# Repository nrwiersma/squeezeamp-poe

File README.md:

# SqueezeAMP PoE

`SqueezeAMP PoE` is an amplifier driven by an ESP32 designed to run [squeezelite-esp32](https://github.com/sle118/squeezelite-esp32), powered by PoE++.

Features:

* Power over Ethernet 802.3bt 60W (PoE++)
* ESP32 WROOM 4MB Flash 8MB PSRAM
* TAS5756 Amplifier capable of driving stereo 30W 8Ohm speakers

## Why

The position of speakers is often not optimal for WiFi, leading to unreliable music streaming. Adding 100Mb ethernet allows
more reliable connections with ample bandwidth. Given an ethernet connection, PoE is able to provide power for the device.

The schematic is inspired by the [SqueezeAMPagain](https://github.com/hallo-alex/SqueezeAMPagain).

## Configuration

Install [squeezelite-esp32](https://github.com/sle118/squeezelite-esp32). The simplest method is to use the [installer](https://sle118.github.io/squeezelite-esp32-installer/).

Set the following configuration via the NVS Editor to configure:

dac_config: `model=TAS57xx,bck=33,ws=25,do=32,sda=27,scl=26,mute=4:0`
eth_config: `model=w5500,cs=15,speed=20000000,intr=18,rst=19`
spi_config: `mosi=13,clk=14,host=1,miso=12,dc=-1`
set_GPIO:   `2=spkfault`

## PCB Fabrication and Assembly by PCBWay

I am proudly sponsored by [PCBWay](https://www.pcbway.com/), a leading manufacturer specializing in PCB prototyping, 
low-volume production, and PCB Assembly services. Thanks to PCBWay’s sponsorship, I was able to fabricate and assemble 
my PCBs with high precision and quality. Their advanced manufacturing capabilities ensured that our design was 
translated into a robust and functional product.

[//]: # (![board image]&#40;assets/pcb.png&#41;)

### Why PCBWay?

PCBWay offers:

* **High-quality PCB fabrication** with multiple layer options, surface finishes, and material choices.
* **Fast turnaround times** to meet project deadlines efficiently.
* **Affordable pricing** for both prototyping and mass production.
* **Reliable PCB assembly services**, including SMT, through-hole, and mixed assembly.
* **Exceptional customer support** and a user-friendly ordering platform.

### Get Your Own PCBs from PCBWay

I highly recommend PCBWay for all your PCB fabrication and assembly needs. Their dedication to quality and customer 
satisfaction makes them an ideal partner for your projects. If you're looking for a trusted partner for PCB fabrication 
and assembly, check out PCBWay for your next project.

Special thanks to PCBWay for their generous support!

## Changelog

#### v0.1.0

* Initial schematic and board

#### v0.1.1

* Fixed W5500 crystal clock not being enabled

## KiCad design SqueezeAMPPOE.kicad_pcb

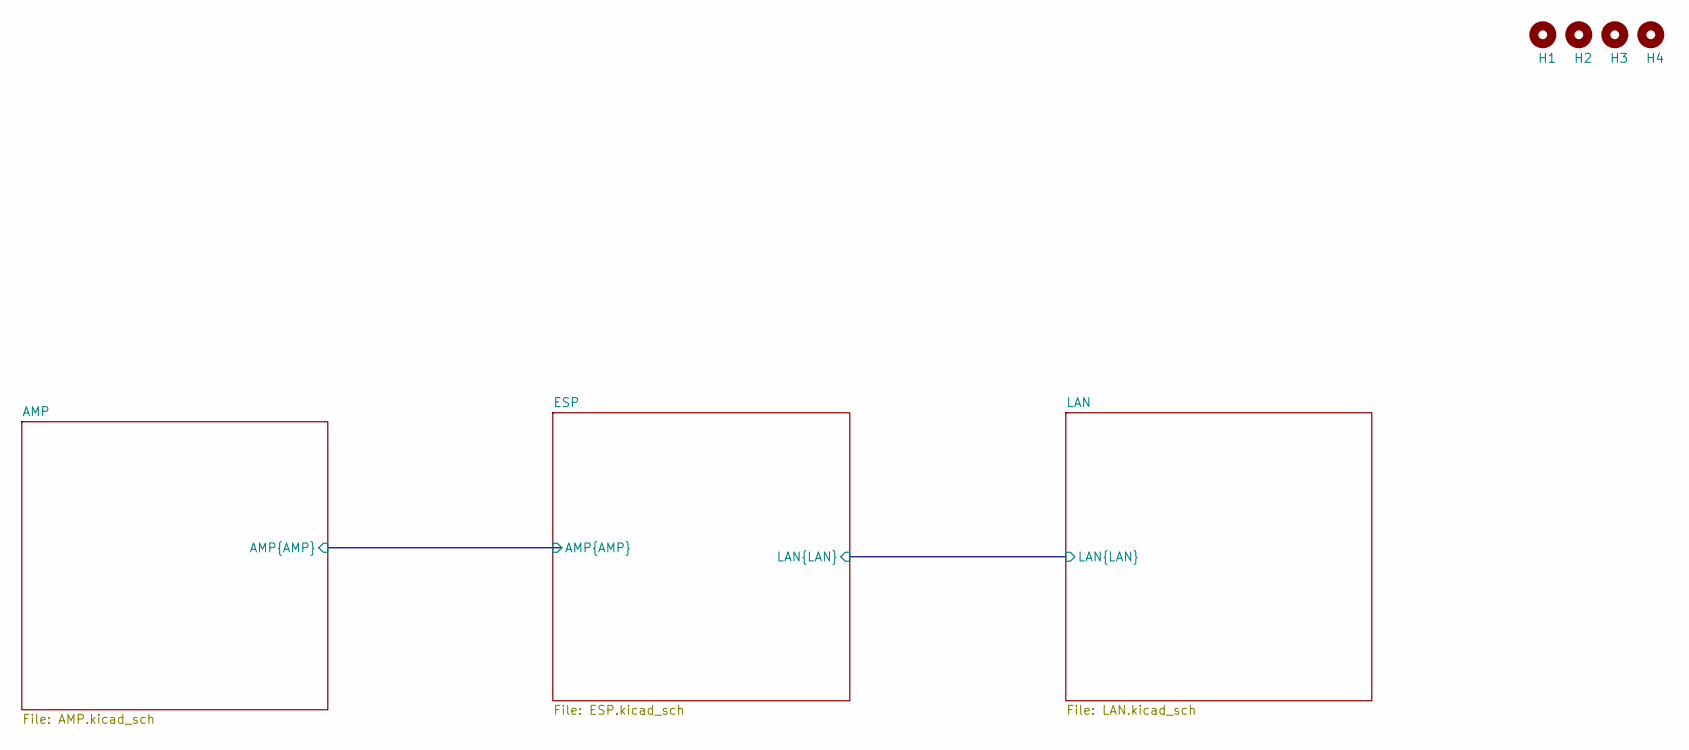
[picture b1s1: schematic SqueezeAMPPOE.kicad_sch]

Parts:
H1, H2, H3, H4: MountingHole; MountingHole_3.2mm_M3

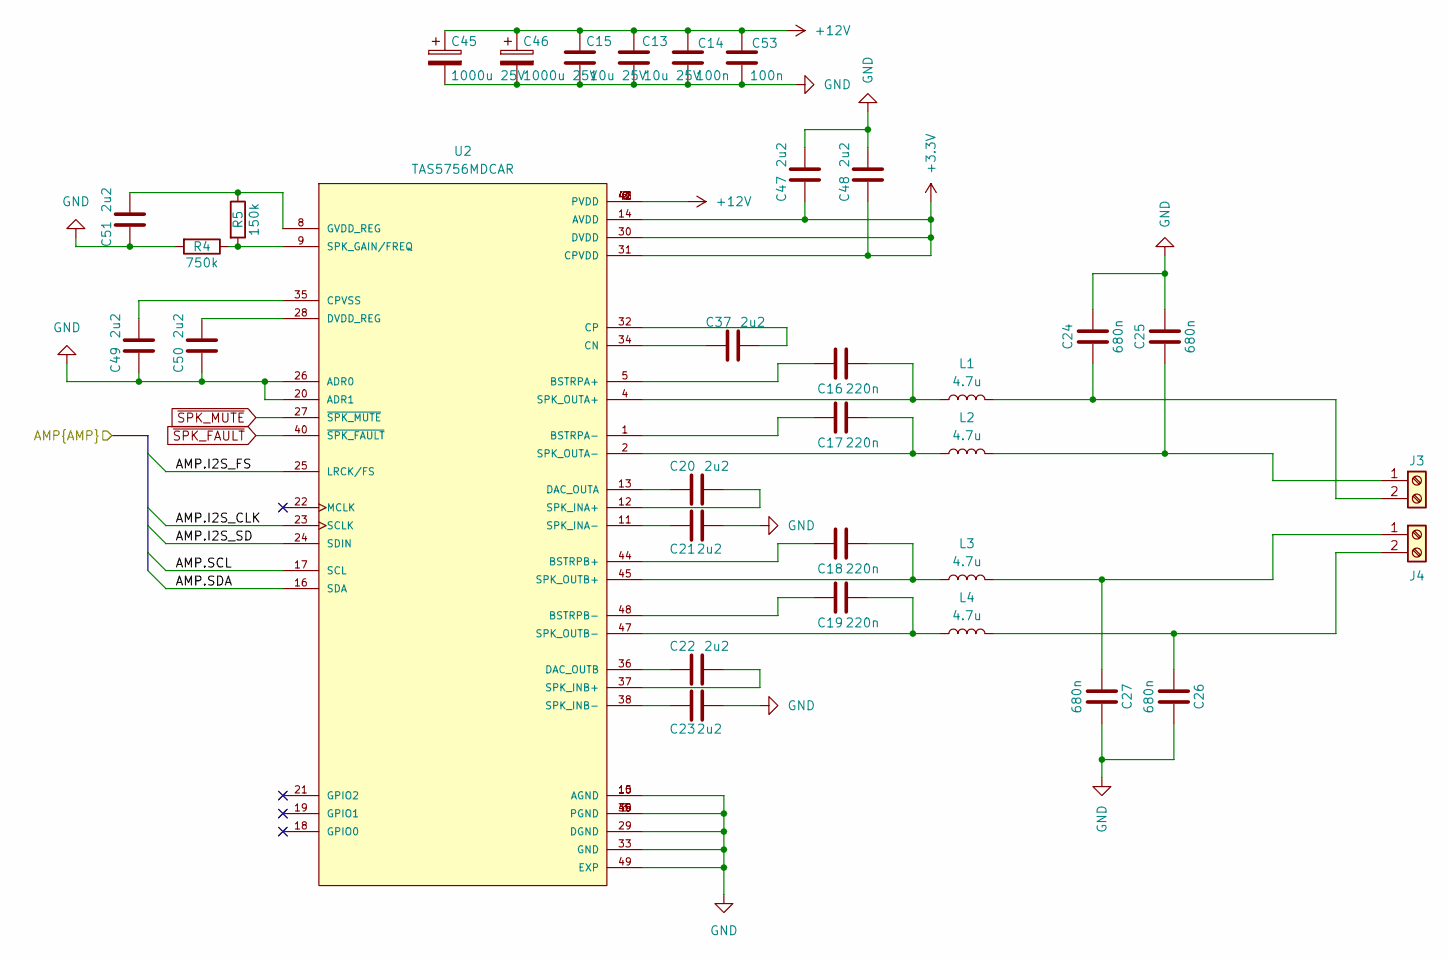
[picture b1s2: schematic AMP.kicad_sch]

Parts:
C13, C15: 10u 25V; C_0603_1608Metric; MPN CL10A106MA8NRNC; JLCPCB Part # C96446
C14, C53: 100n; C_0603_1608Metric; MPN CL10B104KB8NNNC; JLCPCB Part # C1591
C16, C17, C18, C19: 220n; C_0805_2012Metric; MPN CL21B224KBFNNNE; JLCPCB Part # C5378
C20, C21, C22, C23, C37, C47, C48, C49, C50, C51: 2u2; C_0603_1608Metric; MPN CL10A225KA8NNNC; JLCPCB Part # C57895
C24, C25, C26, C27: 680n; C_0805_2012Metric; MPN CC0805KKX7R9BB684; JLCPCB Part # C107133
C45, C46: 1000u 25V; CP_Elec_10x12.5; MPN EFVM025ADA102M10C0; JLCPCB Part # C22387800
J3, J4: Screw_Terminal_01x02; TerminalBlock_Phoenix_MKDS-1,5-2-5.08_1x02_P5.08mm_Horizont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; MPN 1715721; JLCPCB Part # C480516
L1, L2, L3, L4: 4.7u; L_Ferrocore_DLG-0703; MPN SM7850-4R7MT; JLCPCB Part # C52377
R4: 750k; R_0603_1608Metric; MPN RC0603FR-07750KL; JLCPCB Part # C137684
R5: 150k; R_0603_1608Metric; MPN RC0603FR-07150KL; JLCPCB Part # C114660
U2: TAS5756MDCAR; SOP50P810X120-49N; MPN TAS5756MDCAR; JLCPCB Part # C2867541

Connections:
+3.3V: C47.1, C48.1, U2.14 (AVDD), U2.30 (DVDD), U2.31 (CPVDD); also elsewhere on the board
+12V: C13.2, C14.2, C15.2, C45.1, C46.1, C53.2, U2.6 (PVDD), U2.7 (PVDD), U2.41 (PVDD), U2.42 (PVDD), U2.43 (PVDD); also elsewhere on the board
/AMP/AMP.I2S_CLK: U2.23 (SCLK); also elsewhere on the board
/AMP/AMP.I2S_FS: U2.25 (LRCK/FS); also elsewhere on the board
/AMP/AMP.I2S_SD: U2.24 (SDIN); also elsewhere on the board
/AMP/AMP.SCL: U2.17 (SCL); also elsewhere on the board
/AMP/AMP.SDA: U2.16 (SDA); also elsewhere on the board
GND: C13.1, C14.1, C15.1, C21.2, C23.2, C24.2, C25.2, C26.2, C27.2, C45.2, C46.2, C47.2, C48.2, C49.1, C50.1, C51.1, C53.1, R4.2, U2.3 (PGND), U2.10 (AGND), U2.15 (AGND), U2.20 (ADR1), U2.26 (ADR0), U2.29 (DGND), U2.33 (GND), U2.39 (PGND), U2.46 (PGND), U2.49 (EXP); also elsewhere on the board
unnamed: C25.1, J3.1, L2.2
unnamed: C24.1, J3.2, L1.2
unnamed: C27.1, J4.1, L3.2
unnamed: C26.1, J4.2, L4.2
unnamed: C16.1, U2.5 (BSTRPA+)
unnamed: C17.1, U2.1 (BSTRPA-)
unnamed: C18.1, U2.44 (BSTRPB+)
unnamed: C19.1, U2.48 (BSTRPB-)
unnamed: C37.1, U2.34 (CN)
unnamed: C37.2, U2.32 (CP)
unnamed: C49.2, U2.35 (CPVSS)
unnamed: C20.1, U2.13 (DAC_OUTA)
unnamed: C22.1, U2.36 (DAC_OUTB)
unnamed: C50.2, U2.28 (DVDD_REG)
unnamed: C51.2, R5.1, U2.8 (GVDD_REG)
unnamed: R4.1, R5.2, U2.9 (SPK_GAIN/FREQ)
unnamed: C20.2, U2.12 (SPK_INA+)
unnamed: C21.1, U2.11 (SPK_INA-)
unnamed: C22.2, U2.37 (SPK_INB+)
unnamed: C23.1, U2.38 (SPK_INB-)
unnamed: C16.2, L1.1, U2.4 (SPK_OUTA+)
unnamed: C17.2, L2.1, U2.2 (SPK_OUTA-)
unnamed: C18.2, L3.1, U2.45 (SPK_OUTB+)
unnamed: C19.2, L4.1, U2.47 (SPK_OUTB-)
~SPK_FAULT: U2.40 (~SPK_FAULT); also elsewhere on the board
~SPK_MUTE: U2.27 (~SPK_MUTE); also elsewhere on the board

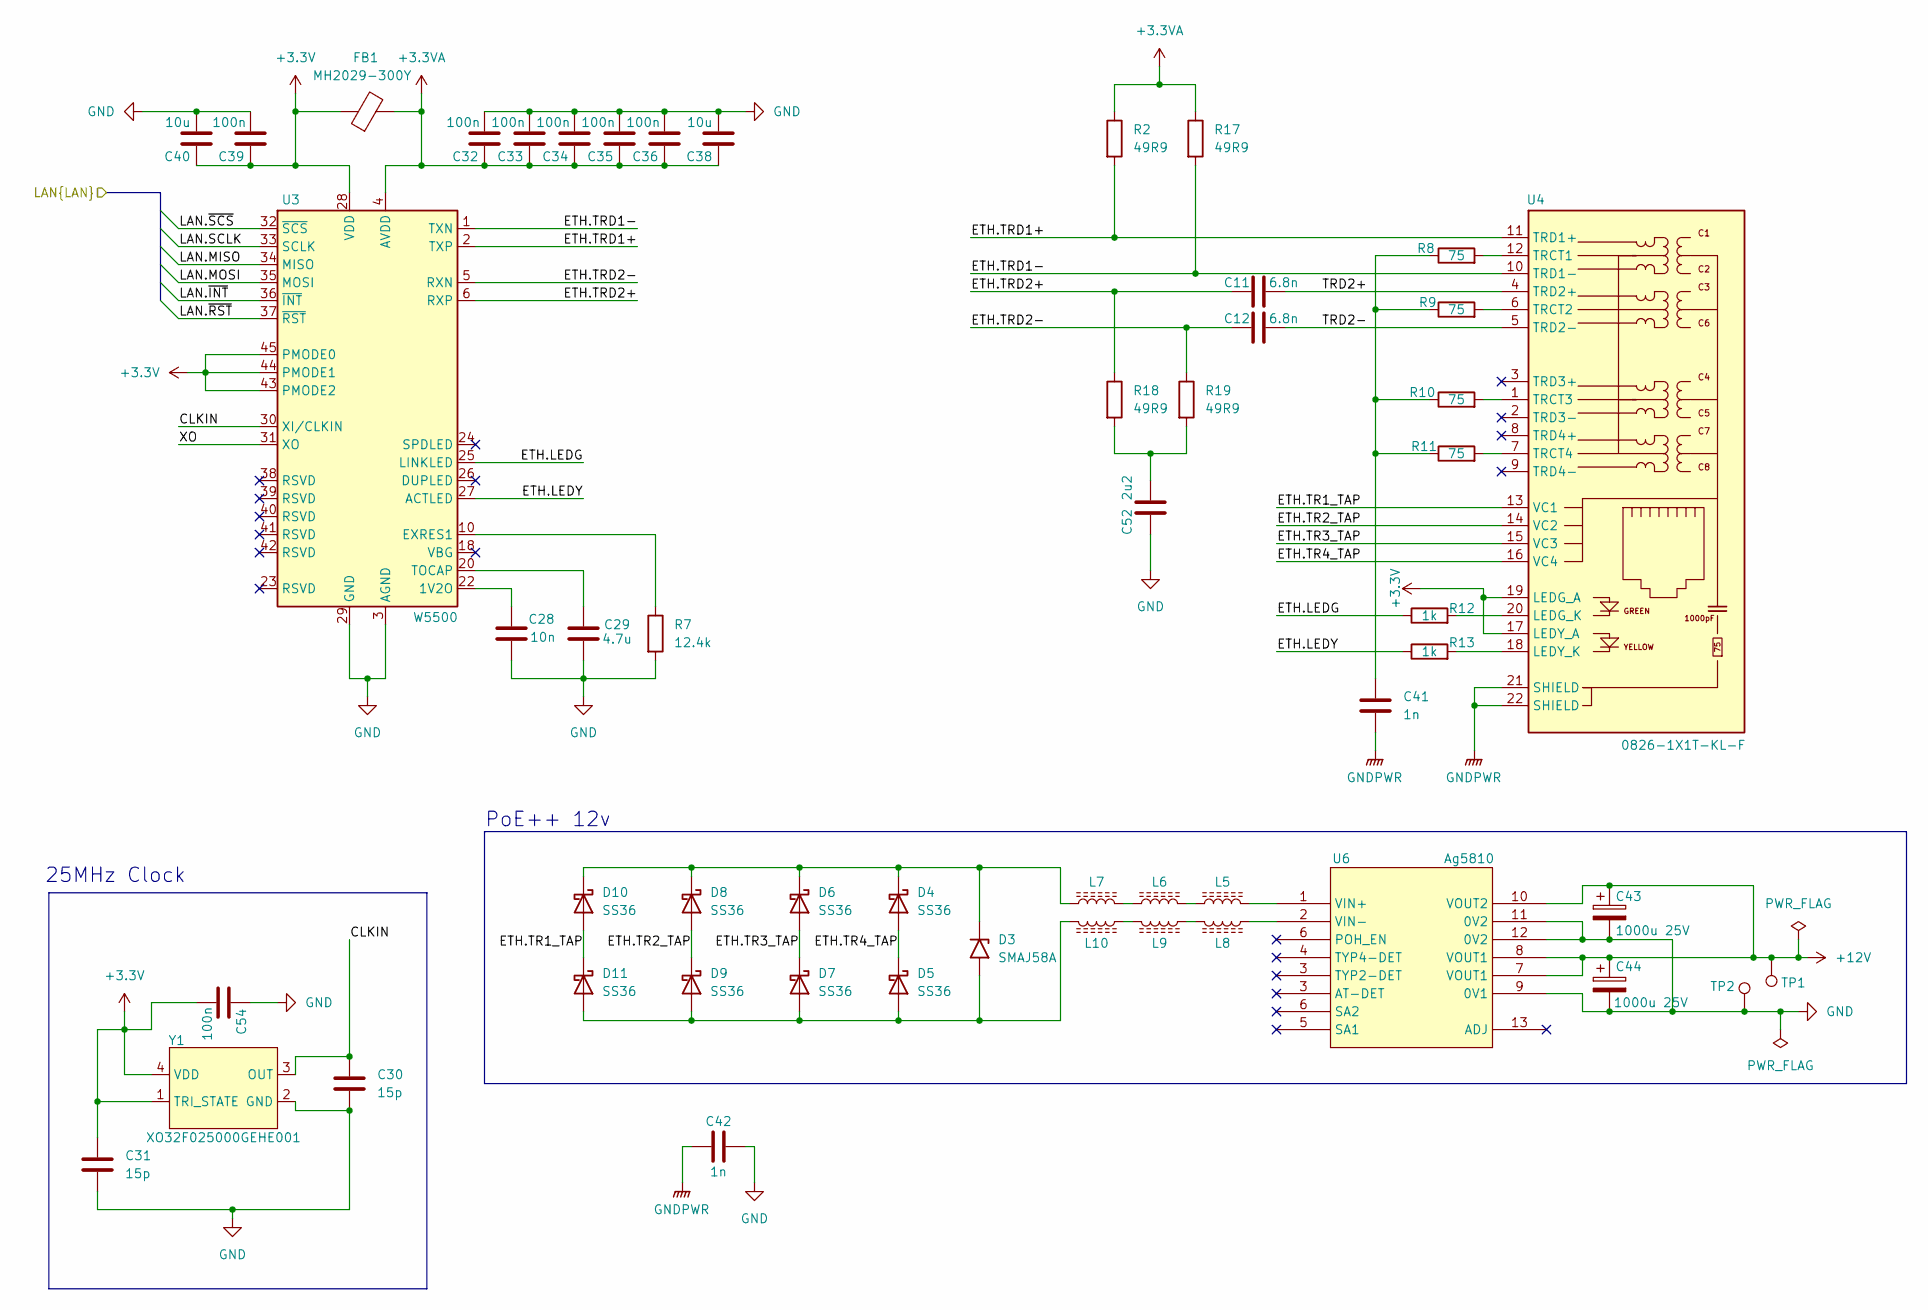
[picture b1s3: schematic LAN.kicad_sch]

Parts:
C11, C12: 6.8n; C_0603_1608Metric; MPN C1608C0G2A682J080AC; JLCPCB Part # C2183110
C28: 10n; C_0603_1608Metric; MPN CL10B103KB8NNNC; JLCPCB Part # C1589
C29: 4.7u; C_0603_1608Metric; MPN CL10A475KP8NNNC; JLCPCB Part # C1705
C30, C31: 15p; C_0603_1608Metric; MPN CL10C150JB8NNNC; JLCPCB Part # C1644
C32, C33, C34, C35, C36, C39, C54: 100n; C_0603_1608Metric; MPN CL10B104KB8NNNC; JLCPCB Part # C1591
C38, C40: 10u; C_0603_1608Metric; MPN CL10A106MA8NRNC; JLCPCB Part # C96446
C41: 1n; C_0603_1608Metric; MPN CL10B102KB8NNNC; JLCPCB Part # C1588
C42: 1n; C_1206_3216Metric; MPN CC1206KKX7RDBB102; JLCPCB Part # C23631
C43, C44: 1000u 25V; CP_Elec_10x12.5; MPN EFVM025ADA102M10C0; JLCPCB Part # C22387800
C52: 2u2; C_0603_1608Metric; MPN CL10A225KA8NNNC; JLCPCB Part # C57895
D3: SMAJ58A; D_SMA; MPN SMAJ58A; JLCPCB Part # C151246
D4, D5, D6, D7, D8, D9, D10, D11: SS36; D_SMA; MPN SS36; JLCPCB Part # C16015
FB1: MH2029-300Y; L0805; MPN MH2029-300Y; JLCPCB Part # C840593
L5, L6, L7, L8, L9, L10: FBMH3225HM102NT; L_1210; MPN FBMH3225HM102NT; JLCPCB Part # C21520
R2, R17, R18, R19: 49R9; R_0603_1608Metric; MPN RC0603FR-0749R9L; JLCPCB Part # C114625
R7: 12.4k; R_0603_1608Metric; MPN RC0603FR-0712K4L; JLCPCB Part # C137798
R8, R9, R10, R11: 75; R_0603_1608Metric; MPN RC0603FR-0775RL; JLCPCB Part # C112309
R12, R13: 1k; R_0603_1608Metric; MPN RC0603JR-071KL; JLCPCB Part # C14676
TP1, TP2: TestPoint; TestPoint_Pad_D2.0mm
U3: W5500; LQFP-48_7x7mm_P0.5mm; MPN W5500; JLCPCB Part # C32843
U4: 0826-1X1T-KL-F; CONN_0826-1X1T-HS-F_BEL; MPN 0826-1X1T-KL-F; JLCPCB Part # C3179906
U6: Ag5810; Converter_DCDC_Silvertel_Ag5810; MPN Ag5810
Y1: XO32F025000GEHE001; SMD3225-4P; MPN XO32F025000GEHE001; JLCPCB Part # C20607963

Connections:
+3.3V: C31.2, C39.1, C40.1, C54.2, FB1.1, U3.28 (VDD), U3.43 (PMODE2), U3.44 (PMODE1), U3.45 (PMODE0), U4.17 (LEDY_A), U4.19 (LEDG_A), Y1.1 (TRI_STATE), Y1.4 (VDD); also elsewhere on the board
+3.3VA: C32.1, C33.1, C34.1, C35.1, C36.1, C38.1, FB1.2, R2.1, R17.1, U3.4 (AVDD), U3.8 (AVDD), U3.11 (AVDD), U3.15 (AVDD), U3.17 (AVDD), U3.21 (AVDD)
+12V: C43.1, C44.1, TP1.1, U6.7 (VOUT1), U6.8 (VOUT1), U6.10 (VOUT2); also elsewhere on the board
/ESP/LAN.MISO: U3.34 (MISO); also elsewhere on the board
/ESP/LAN.MOSI: U3.35 (MOSI); also elsewhere on the board
/ESP/LAN.SCLK: U3.33 (SCLK); also elsewhere on the board
/ESP/LAN.~INT: U3.36 (~INT); also elsewhere on the board
/ESP/LAN.~RST: U3.37 (~RST); also elsewhere on the board
/ESP/LAN.~SCS: U3.32 (~SCS); also elsewhere on the board
/LAN/CLKIN: C30.1, U3.30 (XI/CLKIN), Y1.3 (OUT)
/LAN/ETH.LEDG: R12.1, U3.25 (LINKLED)
/LAN/ETH.LEDY: R13.1, U3.27 (ACTLED)
/LAN/ETH.TR1_TAP: D10.2 (A), D11.1 (K), U4.13 (VC1)
/LAN/ETH.TR2_TAP: D8.2 (A), D9.1 (K), U4.14 (VC2)
/LAN/ETH.TR3_TAP: D6.2 (A), D7.1 (K), U4.15 (VC3)
/LAN/ETH.TR4_TAP: D4.2 (A), D5.1 (K), U4.16 (VC4)
/LAN/ETH.TRD1+: R2.2, U3.2 (TXP), U4.11 (TRD1+)
/LAN/ETH.TRD1-: R17.2, U3.1 (TXN), U4.10 (TRD1-)
/LAN/ETH.TRD2+: C11.1, R18.1, U3.6 (RXP)
/LAN/ETH.TRD2-: C12.1, R19.1, U3.5 (RXN)
/LAN/TRD2+: C11.2, U4.4 (TRD2+)
/LAN/TRD2-: C12.2, U4.5 (TRD2-)
/LAN/XO: U3.31 (XO)
GND: C28.2, C29.2, C30.2, C31.1, C32.2, C33.2, C34.2, C35.2, C36.2, C38.2, C39.2, C40.2, C42.2, C43.2, C44.2, C52.1, C54.1, R7.2, TP2.1, U3.3 (AGND), U3.9 (AGND), U3.14 (AGND), U3.16 (AGND), U3.19 (AGND), U3.29 (GND), U3.48 (AGND), U6.9 (0V1), U6.11 (0V2), U6.12 (0V2), Y1.2 (GND); also elsewhere on the board
GNDPWR: C41.2, C42.1, U4.21 (SHIELD), U4.22 (SHIELD)
unnamed: C41.1, R8.1, R9.1, R10.1, R11.1
unnamed: C52.2, R18.2, R19.2
unnamed: D3.1 (A1), D4.1 (K), D6.1 (K), D8.1 (K), D10.1 (K), L7.1
unnamed: D3.2 (A2), D5.2 (A), D7.2 (A), D9.2 (A), D11.2 (A), L10.2
unnamed: L5.1, L6.2
unnamed: L6.1, L7.2
unnamed: L8.2, L9.1
unnamed: L9.2, L10.1
unnamed: C28.1, U3.22 (1V2O)
unnamed: R7.1, U3.10 (EXRES1)
unnamed: C29.1, U3.20 (TOCAP)
unnamed: R12.2, U4.20 (LEDG_K)
unnamed: R13.2, U4.18 (LEDY_K)
unnamed: R8.2, U4.12 (TRCT1)
unnamed: R9.2, U4.6 (TRCT2)
unnamed: R10.2, U4.1 (TRCT3)
unnamed: R11.2, U4.7 (TRCT4)
unnamed: L5.2, U6.1 (VIN+)
unnamed: L8.1, U6.2 (VIN-)

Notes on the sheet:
PoE++ 12v
25MHz Clock

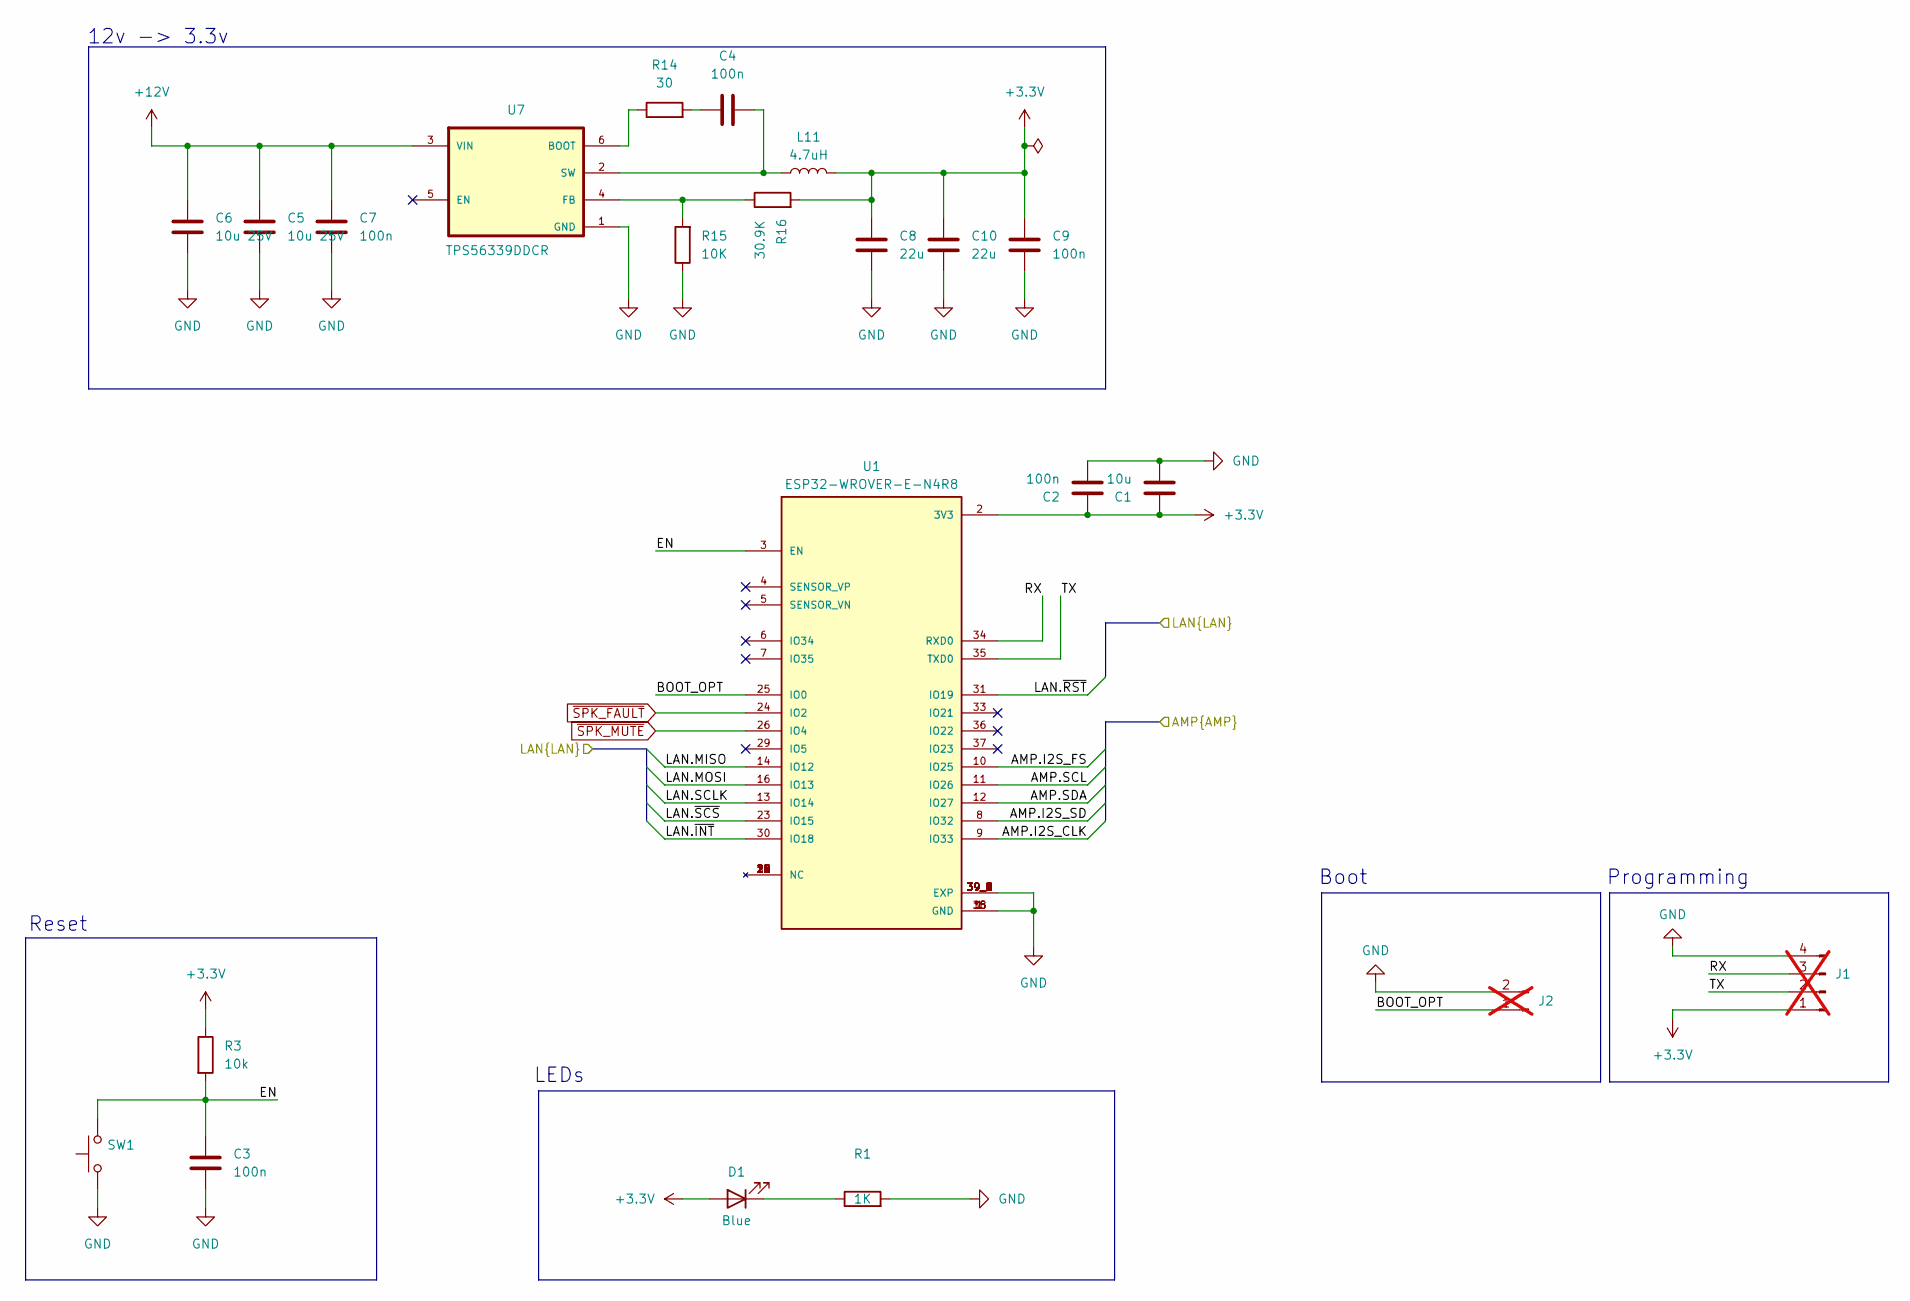
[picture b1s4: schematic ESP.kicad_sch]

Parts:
C1: 10u; C_0603_1608Metric; MPN CL10A106MA8NRNC; JLCPCB Part # C96446
C2, C3, C4, C7, C9: 100n; C_0603_1608Metric; MPN CL10B104KB8NNNC; JLCPCB Part # C1591
C5, C6: 10u 25V; C_0603_1608Metric; MPN CL10A106MA8NRNC; JLCPCB Part # C96446
C8, C10: 22u; C_0603_1608Metric; MPN CL10A226MQ8NRNC; JLCPCB Part # C59461
D1: Blue; LED_0603_1608Metric; MPN LTST-C191TBKT; JLCPCB Part # C99290
J1: Conn_01x04_Pin; PinHeader_1x04_P2.54mm_Vertical; not fitted
J2: Conn_01x02_Pin; PinHeader_1x02_P2.54mm_Vertical; not fitted
L11: 4.7uH; YSPI0530; MPN YSPI0530-4R7M; JLCPCB Part # C351098
R1: 1K; R_0603_1608Metric; MPN ERJ3GEYJ102V; JLCPCB Part # C180848
R3: 10k; R_0603_1608Metric; MPN CR0603AFX-1002EAS; JLCPCB Part # C2091877
R14: 30; R_0603_1608Metric; MPN ERJ3EKF30R0V; JLCPCB Part # C403150
R15: 10K; R_0603_1608Metric; MPN CR0603AFX-1002EAS; JLCPCB Part # C2091877
R16: 30.9K; R_0603_1608Metric; MPN ERJ3EKF3092V; JLCPCB Part # C400664
SW1: SW_Push; K2-1109SP-B4SA-01; MPN K2-1109SP-B4SA-01; JLCPCB Part # C92571
U1: ESP32-WROVER-E-N4R8; XCVR_ESP32-WROVER-E-N4R8; MPN ESP32-WROVER-E-N4R8; JLCPCB Part # C967023
U7: TPS56339DDCR; MPN TPS56339DDCR; JLCPCB Part # C2071106

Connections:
+3.3V: C1.1, C2.1, C8.2, C9.2, C10.2, D1.2 (A), J1.1, L11.2, R3.1, R16.2, U1.2 (3V3); also elsewhere on the board
+12V: C5.2, C6.2, C7.2, U7.3 (VIN); also elsewhere on the board
/AMP/AMP.I2S_CLK: U1.9 (IO33); also elsewhere on the board
/AMP/AMP.I2S_FS: U1.10 (IO25); also elsewhere on the board
/AMP/AMP.I2S_SD: U1.8 (IO32); also elsewhere on the board
/AMP/AMP.SCL: U1.11 (IO26); also elsewhere on the board
/AMP/AMP.SDA: U1.12 (IO27); also elsewhere on the board
/ESP/BOOT_OPT: J2.1, U1.25 (IO0)
/ESP/EN: C3.1, R3.2, SW1.2, U1.3 (EN)
/ESP/LAN.MISO: U1.14 (IO12); also elsewhere on the board
/ESP/LAN.MOSI: U1.16 (IO13); also elsewhere on the board
/ESP/LAN.SCLK: U1.13 (IO14); also elsewhere on the board
/ESP/LAN.~INT: U1.30 (IO18); also elsewhere on the board
/ESP/LAN.~RST: U1.31 (IO19); also elsewhere on the board
/ESP/LAN.~SCS: U1.23 (IO15); also elsewhere on the board
/ESP/RX: J1.3, U1.34 (RXD0)
/ESP/TX: J1.2, U1.35 (TXD0)
GND: C1.2, C2.2, C3.2, C5.1, C6.1, C7.1, C8.1, C9.1, C10.1, J1.4, J2.2, R1.2, R15.1, SW1.1, U1.1 (GND), U1.15 (GND), U1.38 (GND), U1.39_1 (EXP), U1.39_2 (EXP), U1.39_3 (EXP), U1.39_4 (EXP), U1.39_5 (EXP), U1.39_6 (EXP), U1.39_7 (EXP), U1.39_8 (EXP), U1.39_9 (EXP), U7.1 (GND); also elsewhere on the board
unnamed: C4.1, R14.2
unnamed: D1.1 (K), R1.1
unnamed: R14.1, U7.6 (BOOT)
unnamed: R15.2, R16.1, U7.4 (FB)
unnamed: C4.2, L11.1, U7.2 (SW)
~SPK_FAULT: U1.24 (IO2); also elsewhere on the board
~SPK_MUTE: U1.26 (IO4); also elsewhere on the board

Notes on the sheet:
Boot
LEDs
12v -> 3.3v
Reset
Programming

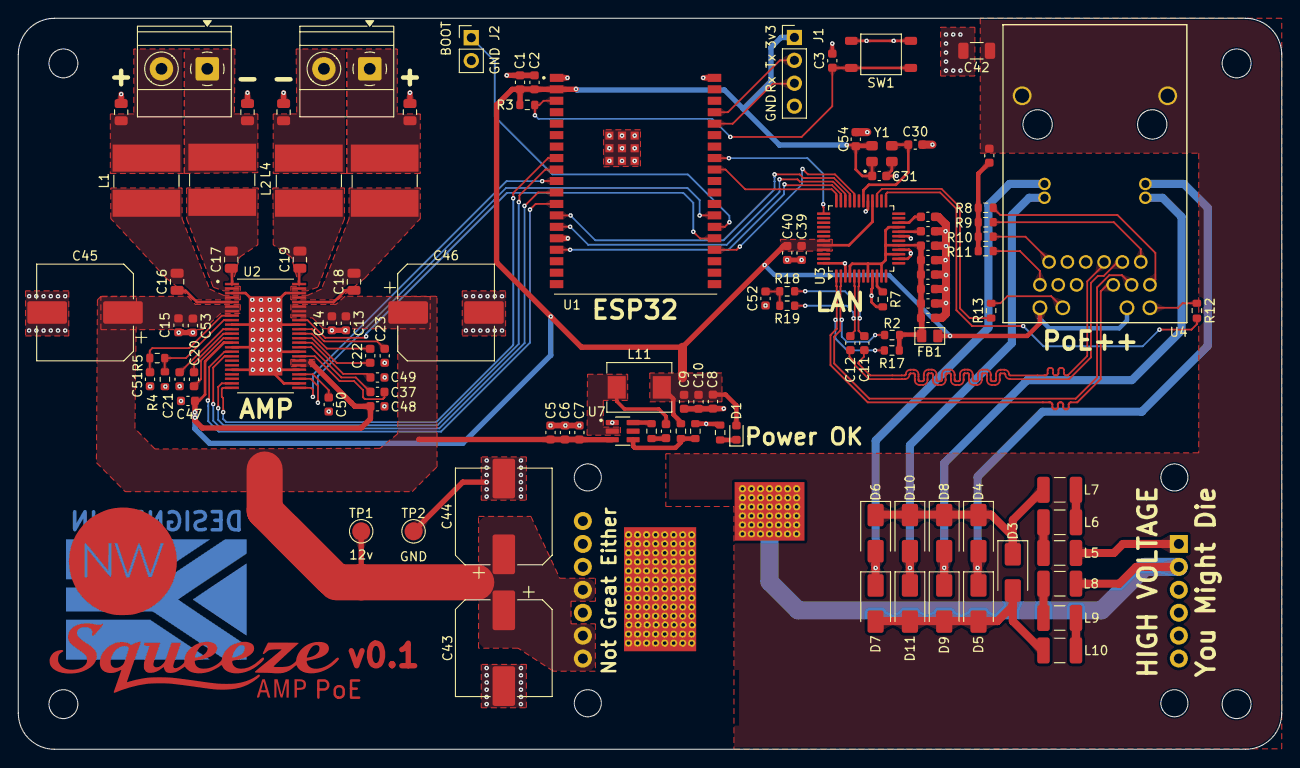
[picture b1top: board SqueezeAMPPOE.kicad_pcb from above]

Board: 4 copper layers, 140.0 x 81.0 mm, 112 parts (1 on the bottom side), 83 nets.

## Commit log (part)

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2025-04-15 chore: initial commit
2025-05-08 feat: initial board
2025-05-08 feat: initial board (#1)
2025-05-30 feat: add README image
2025-05-31 fix: crystal clock enable pin to 3v3
2025-05-31 chore: specify configuration in the README
2025-05-31 chore: update README changelog
2025-06-02 feat: add case models
2025-06-02 feat: add case models (#2)

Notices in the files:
README.md:
License: MIT
